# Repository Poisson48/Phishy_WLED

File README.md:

Phishy_WLED is a simple board to drive LED with the help of WLED software. It's based on esp32, it's fully open-source and i will probably sell some boards on etsy soon.

## Features
- RGBWWW LED strip support
- WS2182B ( or any ws18 someting ) LED strip support
- input from 5V to 60V
- pulled up inputs

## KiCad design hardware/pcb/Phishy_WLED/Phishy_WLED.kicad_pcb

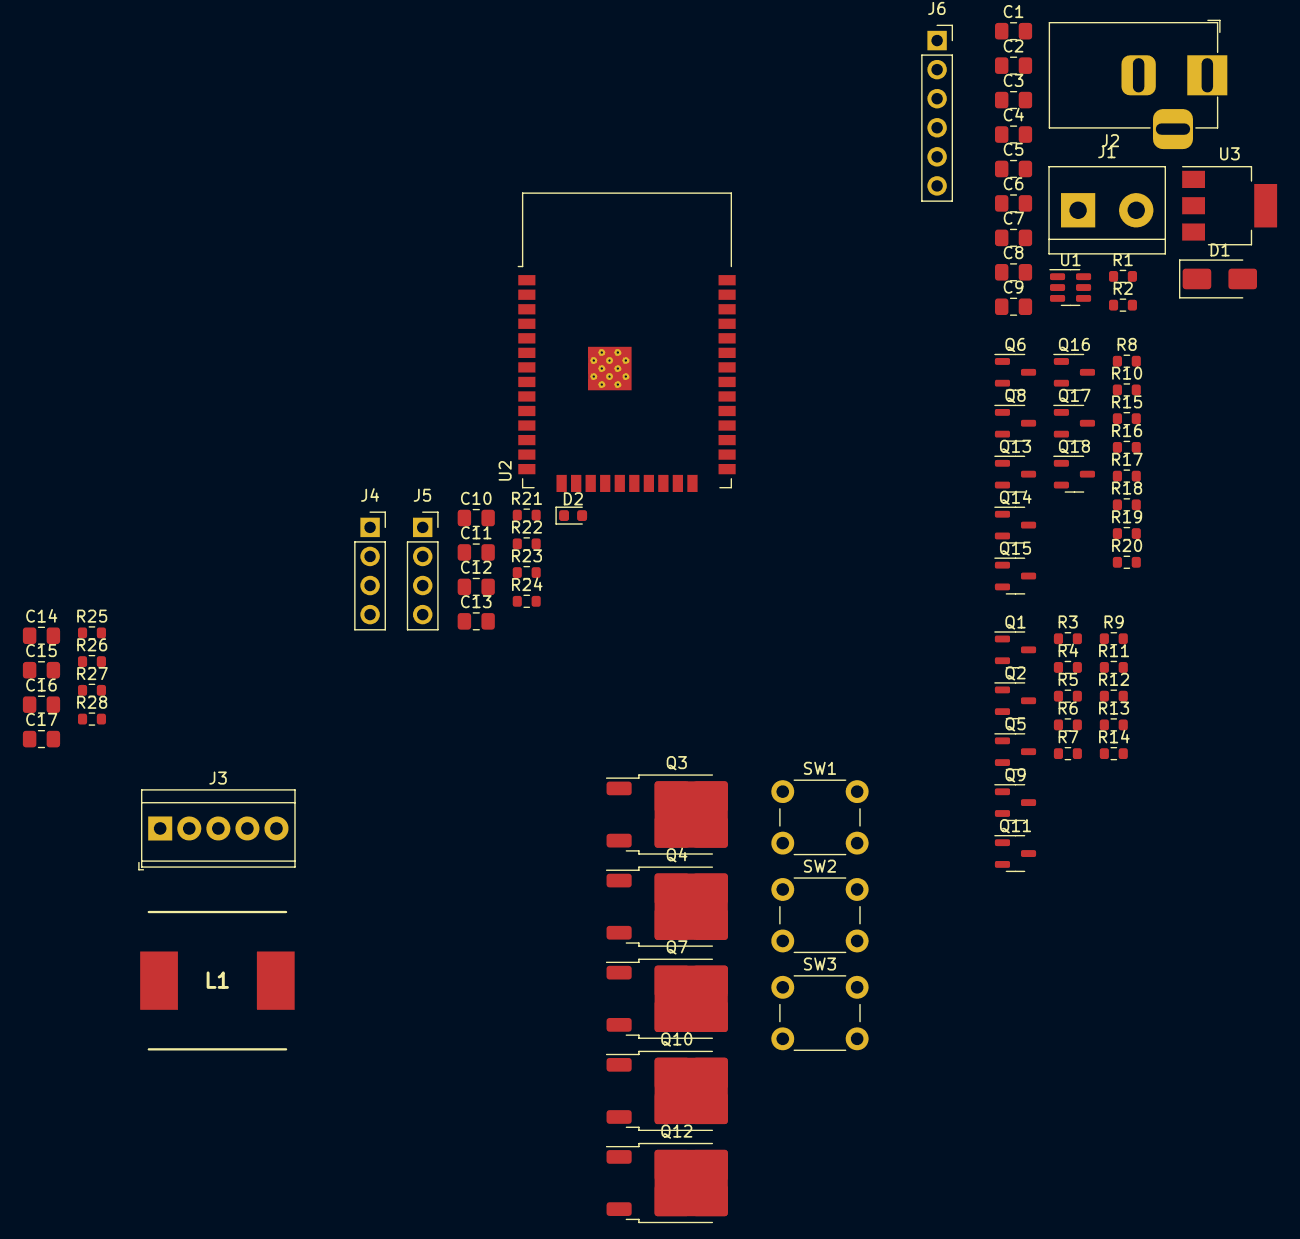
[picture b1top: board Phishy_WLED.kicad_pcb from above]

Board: 2 copper layers, 78 parts (0 on the bottom side), 54 nets, no tracks yet.

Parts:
C1, C3, C5, C6, C8, C10, C13, C14, C15, C16, C17: 100nF; C_0805_2012Metric_Pad1.18x1.45mm_HandSolder
C2, C4, C7, C9, C11, C12: 10uF; C_0805_2012Metric_Pad1.18x1.45mm_HandSolder
D1: D_Schottky; D_SMA
D2: LED; LED_0603_1608Metric
J1: Screw_Terminal_01x02; TerminalBlock_bornier-2_P5.08mm
J2: Barrel_Jack_Switch; BarrelJack_Horizontal
J3: Screw_Terminal_01x05; TerminalBlock_TE_282834-5_1x05_P2.54mm_Horizontal
J4, J5: Screw_Terminal_01x04; PinSocket_1x04_P2.54mm_Vertical
J6: Conn_01x06; PinSocket_1x06_P2.54mm_Vertical
L1: 22uH; INDPM120120X800N
Q1, Q2, Q5, Q6, Q8, Q9, Q11, Q15, Q16: 2N7002L; SOT-23-3
Q3, Q4, Q7, Q10, Q12: IRFR1205TRPBF; TO-252-2
Q13, Q14, Q17, Q18: BSS138; SOT-23-3
R1, R2: R; R_0603_1608Metric
R3, R4, R7, R8, R11, R13, R15, R17, R18, R21, R22, R24, R25, R26, R27, R28: 10k; R_0603_1608Metric
R5, R6, R9, R10, R12, R14, R16, R19, R20, R23: 1k; R_0603_1608Metric
SW1, SW2, SW3: SW_Push; SW_PUSH_6mm_H5mm
U1: LMR16006YQ; SOT-23-6
U2: ESP32-WROOM-32D
U3: LM7805MP; SOT-223-3_TabPin2

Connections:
+3.3V: C4.1, C5.1, C10.1, C11.1, J6.3, L1.2, R1.1, R21.2, R22.2, R24.2, R25.2, R26.2, R27.2, R28.2, U2.2 (VDD)
+5V: C8.1, C9.1, R10.2, R16.2, R19.2, R20.2, U3.3 (OUT)
/drivers/in_B: R7.1, U2.28 (IO17)
/drivers/in_G: R4.1, U2.27 (IO16)
/drivers/in_R: R3.1, U2.16 (IO13)
/drivers/in_W: R11.1, U2.30 (IO18)
/drivers/in_WW: R13.1, U2.31 (IO19)
/drivers/out_B: J3.3, Q7.2 (D)
/drivers/out_G: J3.2, Q4.2 (D)
/drivers/out_R: J3.1, Q3.2 (D)
/drivers/out_W: J3.4, Q10.2 (D)
/drivers/out_WW: J3.5, Q12.2 (D)
/pulls_ups/pull_input_ext_1: C14.1, J5.1, R25.1, U2.11 (IO26)
/pulls_ups/pull_input_ext_2: C15.1, J5.2, R26.1, U2.12 (IO27)
/pulls_ups/pull_input_ext_3: C16.1, J5.3, R27.1, U2.8 (IO32)
/pulls_ups/pull_input_ext_4: C17.1, J5.4, R28.1, U2.9 (IO33)
/ws28xx_LEDs/in_DATA_1: R8.1, U2.33 (IO21)
/ws28xx_LEDs/in_DATA_2: R15.1, U2.36 (IO22)
/ws28xx_LEDs/in_DATA_3: R17.1, U2.37 (IO23)
/ws28xx_LEDs/in_DATA_4: R18.1, U2.10 (IO25)
/ws28xx_LEDs/out_DATA_1: J4.1, Q13.3 (D)
/ws28xx_LEDs/out_DATA_2: J4.2, Q14.3 (D)
/ws28xx_LEDs/out_DATA_3: J4.3, Q17.3 (D)
/ws28xx_LEDs/out_DATA_4: J4.4, Q18.3 (D)
EN: C12.1, J6.5, R21.1, SW2.2, U2.3 (EN)
unnamed: C3.2, D1.1 (K), L1.1, U1.6 (SW)
unnamed: D2.2 (A), R23.2
unnamed: Q1.2 (B), R3.2
unnamed: Q1.1 (C), Q3.1 (G), R5.1
unnamed: Q2.2 (B), R4.2
unnamed: Q2.1 (C), Q4.1 (G), R6.1
unnamed: Q5.2 (B), R7.2
unnamed: Q5.1 (C), Q7.1 (G), R9.1
unnamed: Q6.2 (B), R8.2
unnamed: Q8.2 (B), R15.2
unnamed: Q9.2 (B), R11.2
unnamed: Q9.1 (C), Q10.1 (G), R12.1
unnamed: Q11.2 (B), R13.2
unnamed: Q11.1 (C), Q12.1 (G), R14.1
unnamed: Q6.1 (C), Q13.1 (G), R10.1
unnamed: Q8.1 (C), Q14.1 (G), R16.1
unnamed: Q15.2 (B), R17.2
unnamed: Q15.1 (C), Q17.1 (G), R19.1
unnamed: Q16.2 (B), R18.2
unnamed: Q16.1 (C), Q18.1 (G), R20.1
unnamed: C3.1, U1.1 (CB)
unnamed: R1.2, R2.1, U1.3 (FB)
unnamed: R22.1, SW1.1, U2.25 (IO0)
unnamed: R23.1, U2.24 (IO2)
unnamed: C13.1, R24.1, SW3.1, U2.26 (IO4)
RST: C1.2, C2.2, C4.2, C5.2, C6.2, C7.2, C8.2, C9.2, C10.2, C11.2, C12.2, C13.2, C14.2, C15.2, C16.2, C17.2, D1.2 (A), D2.1 (K), J1.2, J2.2, J2.3, J6.4, J6.6, Q1.3 (E), Q2.3 (E), Q3.3 (S), Q4.3 (S), Q5.3 (E), Q6.3 (E), Q7.3 (S), Q8.3 (E), Q9.3 (E), Q10.3 (S), Q11.3 (E), Q12.3 (S), Q13.2 (S), Q14.2 (S), Q15.3 (E), Q16.3 (E), Q17.2 (S), Q18.2 (S), R2.2, SW1.2, SW2.1, SW3.2, U1.2 (GND), U2.1 (GND), U2.15 (GND), U2.38 (GND), U2.39 (GND), U3.2 (GND)
RX: J6.2, U2.34 (RXD0/IO3)
TX: J6.1, U2.35 (TXD0/IO1)
VCC: C1.1, C2.1, C6.1, C7.1, J1.1, J2.1, R5.2, R6.2, R9.2, R12.2, R14.2, U1.5 (VIN), U3.1 (IN)

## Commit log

2023-11-14 basic schematic
    the basic schematic is finished, need to add the footprints and begin the placement
2023-11-14 footprints added !
    all the footprints are here
